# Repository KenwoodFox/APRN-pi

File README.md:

# APRN-pi

[APRN](http://www.aprs.org/aprn.html) was a format i stumbled upon ages ago and thought it looked super cool!

I decided to try making a custom raspberry pi hat that would use the DRA818V (or DRA818U) for aprn.

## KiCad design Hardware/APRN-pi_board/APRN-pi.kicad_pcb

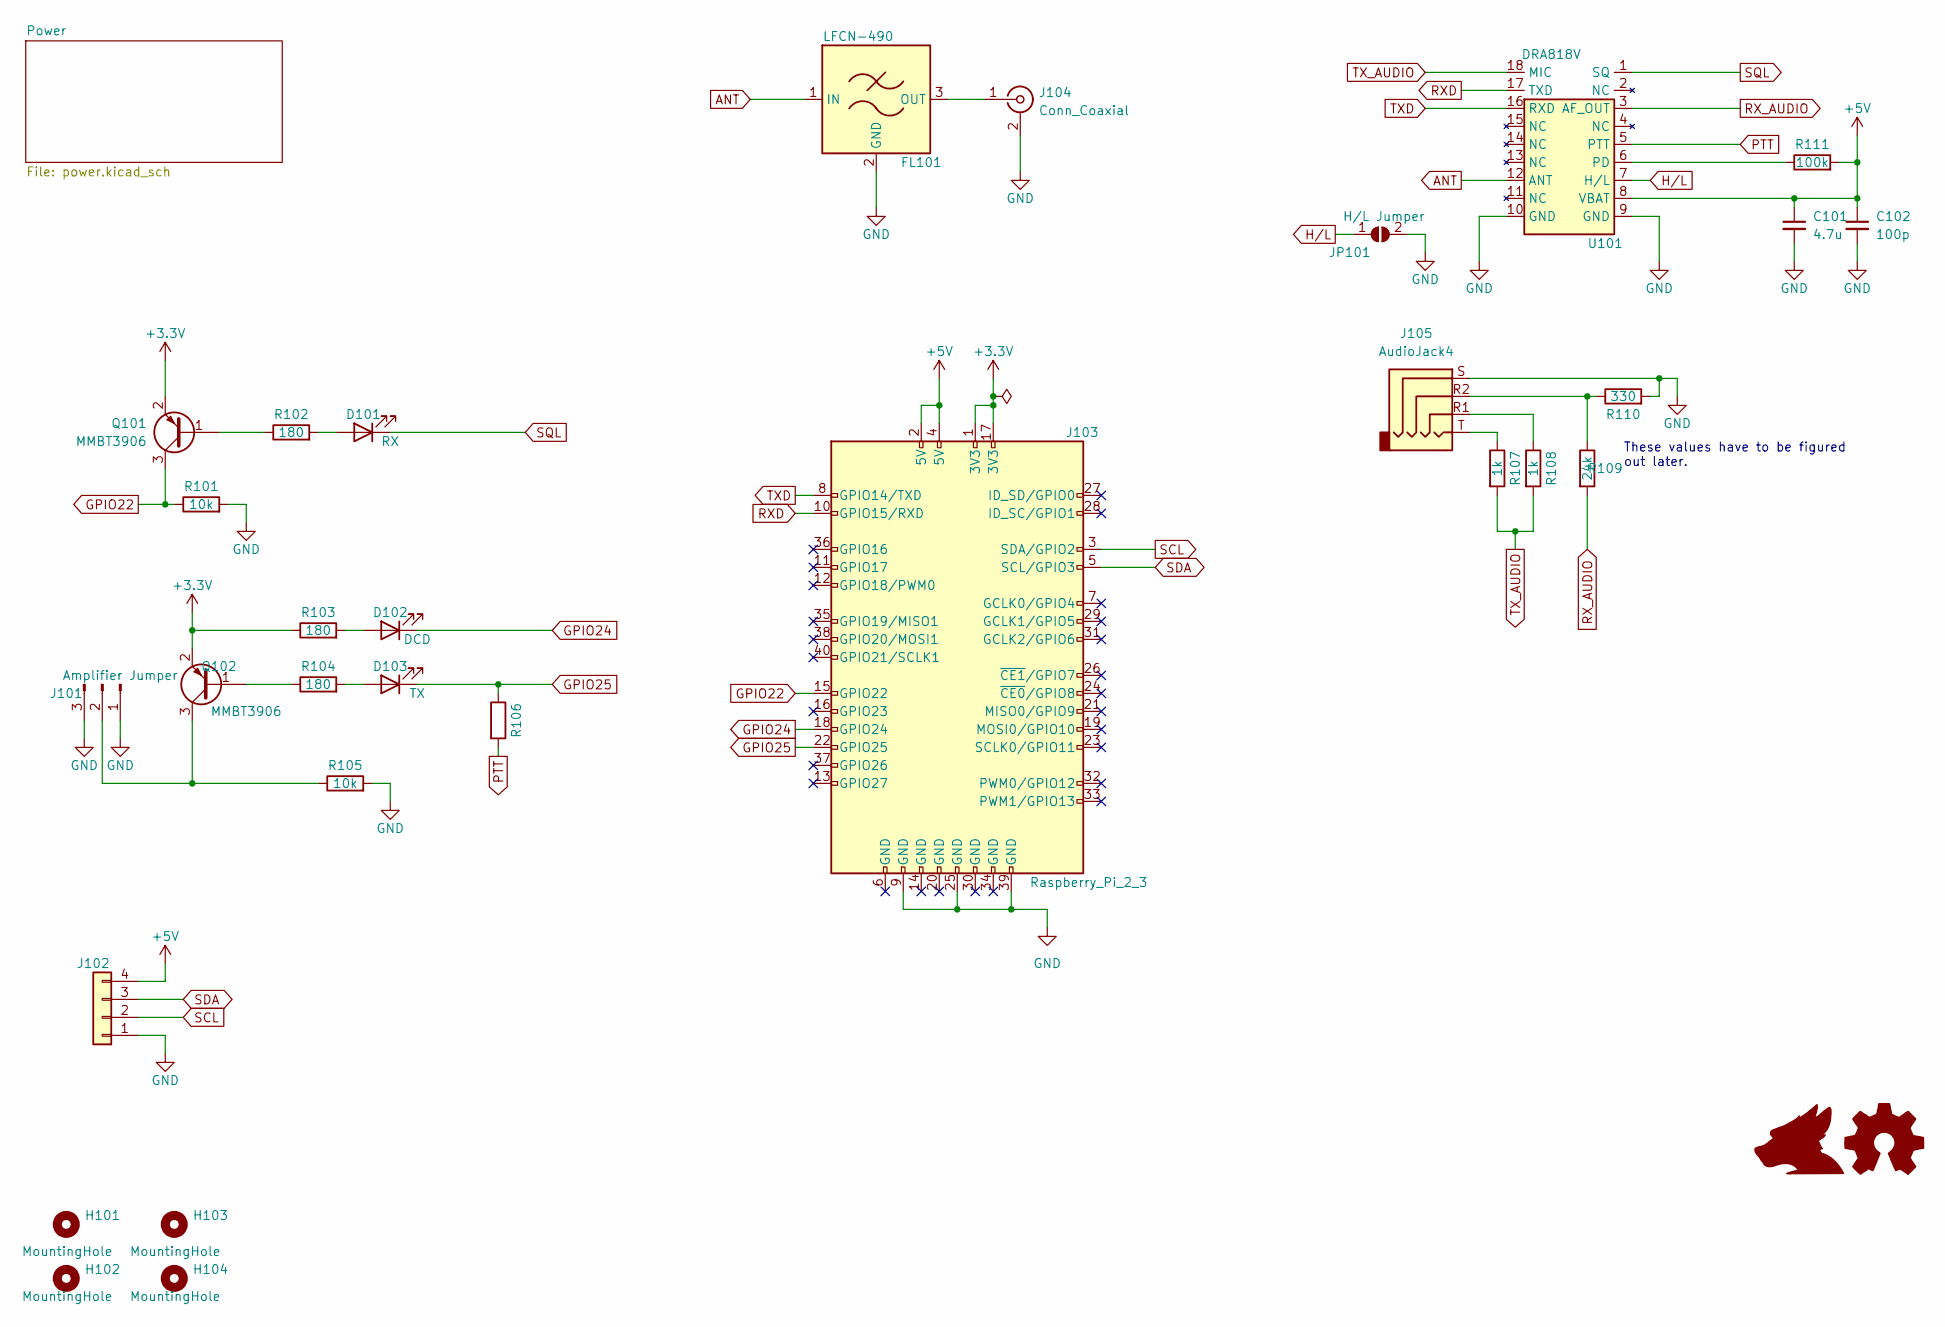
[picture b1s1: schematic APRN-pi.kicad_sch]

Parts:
C101: 4.7u; C_0805_2012Metric
C102: 100p; C_0805_2012Metric
D101: RX; LED_0603_1608Metric
D102: DCD; LED_0603_1608Metric
D103: TX; LED_0603_1608Metric
FL101: LFCN-490; Filter_Mini-Circuits_FV1206
H101, H102, H103, H104: MountingHole; MountingHole_2.7mm
J101: Amplifier Jumper; JST_GH_SM03B-GHS-TB_1x03-1MP_P1.25mm_Horizontal
J102: (no value)
J103: Raspberry_Pi_2_3; PinSocket_2x20_P2.54mm_Vertical
J104: Conn_Coaxial; SMA_Amphenol_132291_Vertical
J105: AudioJack4; Jack_3.5mm_PJ320E_Horizontal
JP101: H/L Jumper; SolderJumper-2_P1.3mm_Open_TrianglePad1.0x1.5mm
Q101, Q102: MMBT3906; SOT-23
R101, R105: 10k; R_0805_2012Metric
R102, R103, R104: 180; R_0805_2012Metric
R106: R_0805_2012Metric
R107, R108: 1k; R_0805_2012Metric
R109: 24k; R_0805_2012Metric
R110: 330; R_0805_2012Metric
R111: 100k; R_0805_2012Metric
U101: DRA818V

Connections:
+3V3: J103.1 (3V3), J103.17 (3V3), Q101.2 (E), Q102.2 (E), R103.1
+5V: C101.1, C102.1, J102.4, J103.2 (5V), J103.4 (5V), R111.2, U101.8 (VBAT); also elsewhere on the board
ANT: FL101.1 (IN), U101.12 (ANT)
GND: C101.2, C102.2, FL101.2 (GND), FL101.4 (GND), J101.1, J101.3, J102.1, J103.9 (GND), J103.25 (GND), J103.39 (GND), J104.2 (Ext), J105.S, JP101.2 (B), R101.2, R105.2, R110.2, U101.9 (GND), U101.10 (GND); also elsewhere on the board
GPIO22: J103.15 (GPIO22), Q101.3 (C), R101.1
GPIO24: D102.1 (K), J103.18 (GPIO24)
GPIO25: D103.1 (K), J103.22 (GPIO25), R106.1; also elsewhere on the board
H/L: JP101.1 (A), U101.7 (H/L)
unnamed: D101.2 (A), R102.2
unnamed: D102.2 (A), R103.2
unnamed: D103.2 (A), R104.2
unnamed: FL101.3 (OUT), J104.1 (In)
unnamed: J101.2, Q102.3 (C), R105.1
unnamed: J105.R1, R108.1
unnamed: J105.R2, R109.1, R110.1
unnamed: J105.T, R107.1
unnamed: Q101.1 (B), R102.1
unnamed: Q102.1 (B), R104.1
unnamed: R111.1, U101.6 (PD)
PTT: R106.2, U101.5 (PTT)
RXD: J103.10 (GPIO15/RXD), U101.17 (TXD)
RX_AUDIO: R109.2, U101.3 (AF_OUT)
SCL: J102.2, J103.3 (SDA/GPIO2)
SDA: J102.3, J103.5 (SCL/GPIO3)
SQL: D101.1 (K), U101.1 (SQ)
TXD: J103.8 (GPIO14/TXD), U101.16 (RXD)
TX_AUDIO: R107.2, R108.2, U101.18 (MIC)

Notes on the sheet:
These values have to be figured out later.

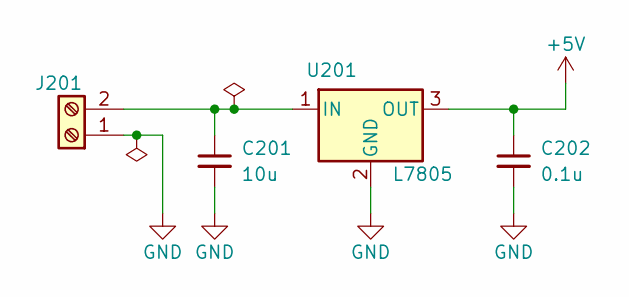
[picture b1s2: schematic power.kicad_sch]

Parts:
C201: 10u; C_0805_2012Metric
C202: 0.1u; C_0805_2012Metric
J201: TerminalBlock_bornier-2_P5.08mm
U201: L7805; TO-220-3_Vertical

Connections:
+5V: C202.1, U201.3 (OUT); also elsewhere on the board
GND: C201.2, C202.2, J201.1, U201.2 (GND); also elsewhere on the board
unnamed: C201.1, J201.2, U201.1 (IN)

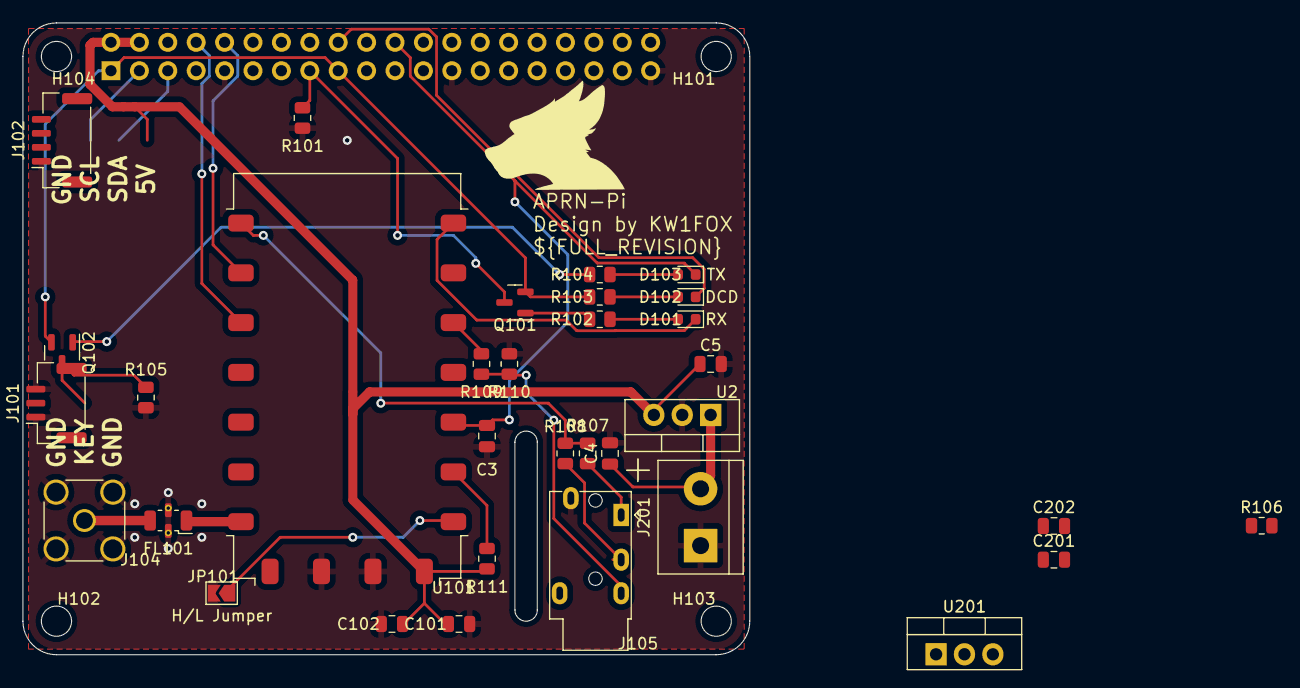
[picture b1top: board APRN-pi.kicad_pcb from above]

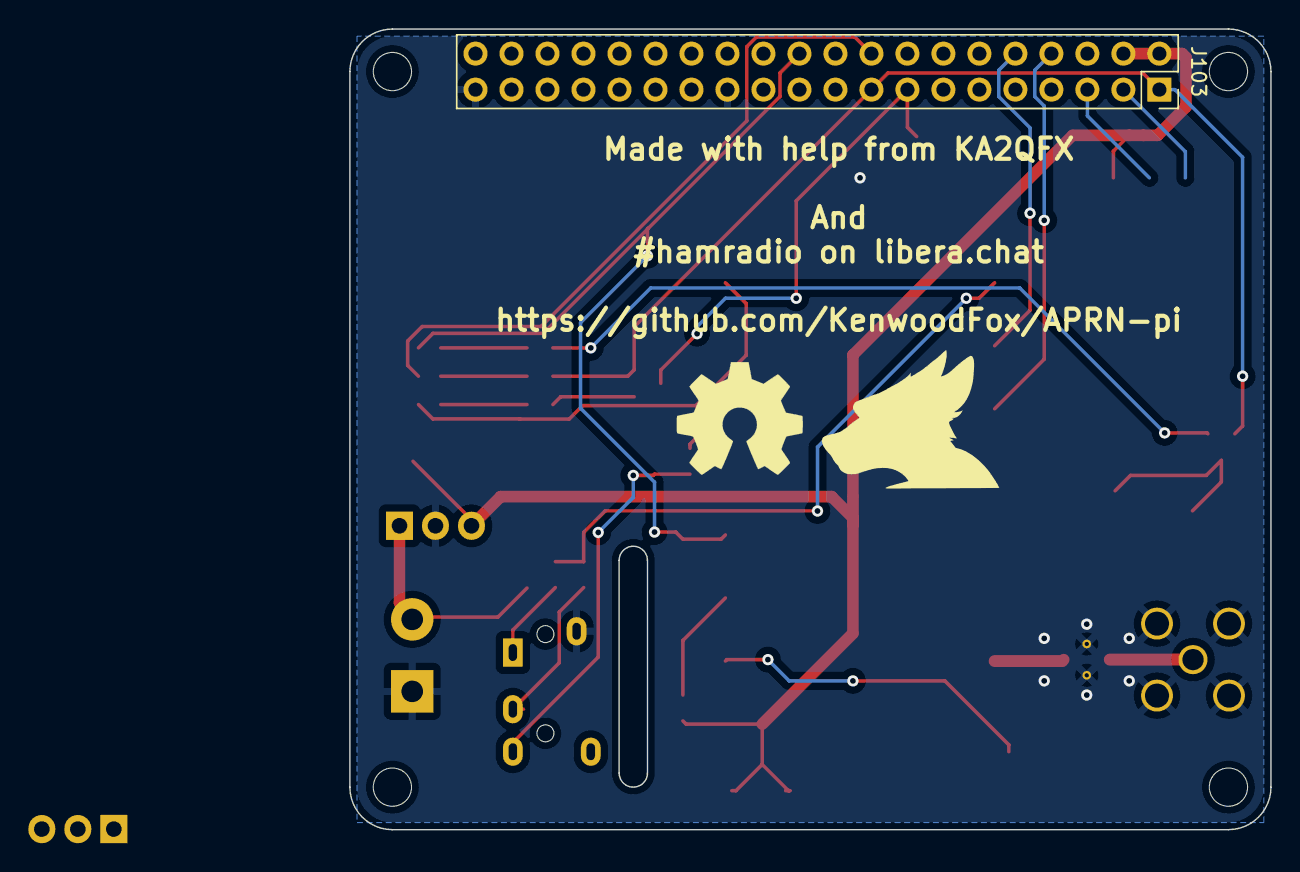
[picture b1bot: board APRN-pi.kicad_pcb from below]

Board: 2 copper layers, 65.0 x 56.5 mm, 40 parts (2 on the bottom side), 29 nets.

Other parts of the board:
C3: 1n; C_0805_2012Metric
C4: 10u; C_0805_2012Metric
C5: 0.1u; C_0805_2012Metric
L1, L2: KITSUNE_LOGO
U2: L7805; TO-220-3_Vertical

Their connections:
+5V: C5.1, U2.3 (OUT); also elsewhere on the board
GND: C3.2, C4.2, C5.2, U2.2 (GND); also elsewhere on the board
GPIO25: C3.1; also elsewhere on the board
unnamed: C4.1, U2.1 (IN)

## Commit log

2022-04-01 init to commit it
2022-04-01 Fix some naming
2022-04-01 try this
2022-04-01 Disable step for now, come back to it later
2022-04-01 More testing
2022-04-01 Try edgy
2022-04-01 Fix docs
2022-04-01 Fix dox
2022-04-01 Final touchups
2022-04-01 Begin work on proper prototype
2022-04-01 Prep board for proper acurate layout
2022-04-01 Bump submodules
2022-04-01 Bump lib color
2022-04-01 Yay!
2022-04-01 Fix image scaling
2022-04-01 Try building gerbers
2022-04-01 Gerber release
2022-04-02 fixup! Gerber release
2022-04-02 Verbose docs
2022-04-02 Custom publisher
2022-04-02 Include updates from kenwoodfox-libraries
2022-04-02 Add some fluff to schematic
2022-04-02 Fix DRC
2022-04-02 Fix DRC again
2022-04-02 attempt 3d renders
2022-04-02 Upload render too
2022-04-02 Make revision caps
2022-04-02 PCB green is the only way to go.
2022-04-02 fixup! PCB green is the only way to go.
2022-04-02 Add more fluff
2022-04-02 Ground plane
2022-04-02 Fix clearances
2022-04-02 Add drc check to actions
2022-04-02 fixup! Add drc check to actions
2022-04-02 Finally fix drc?
2022-04-02 fixup! Finally fix drc?
2022-04-02 Add RF components into schematic
2022-04-02 Bump render quality
2022-04-02 fixup! Bump render quality
2022-04-02 Bump to new logo and add logo
2022-04-02 Clean up naming
2022-04-02 Import last of dimms from pi
2022-04-02 Fix RF stuff with help from @Gandalf#1068
    Co-Authored By: @ka2qfx
2022-04-02 Even more fixups, thx!
    Co-Authored By: @ka2qfx
2022-04-02 Flip header correct direction
2022-04-02 Scootch logo
2022-04-02 Hook up voltage regulator
2022-04-03 More power and audio cleanup
2022-04-04 GPIO22 should read input rx as input
2022-04-04 Clean schematic a little
2022-04-04 More cleanup
2022-04-04 Add h/l jumper
2022-04-04 Use new upstream wrl model
2022-04-04 Patch self
2022-04-04 Add thanks
    @ka2qfx
2022-04-05 Bump upstream
2022-04-05 add i2c breakout
2022-04-05 This board will tottally need a rewiring
2022-04-05 misc
2022-04-05 more logos
2022-04-05 Use upstream
2022-04-05 Bump library
2022-04-05 Do some pcb layout
2022-04-05 Refactor wiring
2022-04-06 transition to netclasses
2022-04-06 Improve accuracy of 50ohm
2022-04-06 fixup lettering
2022-04-06 Proper Prototype (#1)
2022-04-06 Add cool renders
2022-04-06 Bump image
2022-04-06 Bump again
2022-04-06 Bump again!
2022-04-06 Drop colors
2022-04-06 Add renders section
2022-04-06 Dont need gitpython
2022-04-07 Bump colors
2022-04-07 More 3d models
2022-04-07 bump docs
2022-04-19 Inital mess
2022-04-27 Bump kicad libs in aprn-pi
2022-04-27 Bump kicad libs in aprn-pi2
2022-04-29 Bump lib
2022-04-29 Bump logo
2022-04-30 Add reference degs
2022-05-04 This is half baked
